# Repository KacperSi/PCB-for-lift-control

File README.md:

# PCB-for-lift-control
PCB design created in KiCad.

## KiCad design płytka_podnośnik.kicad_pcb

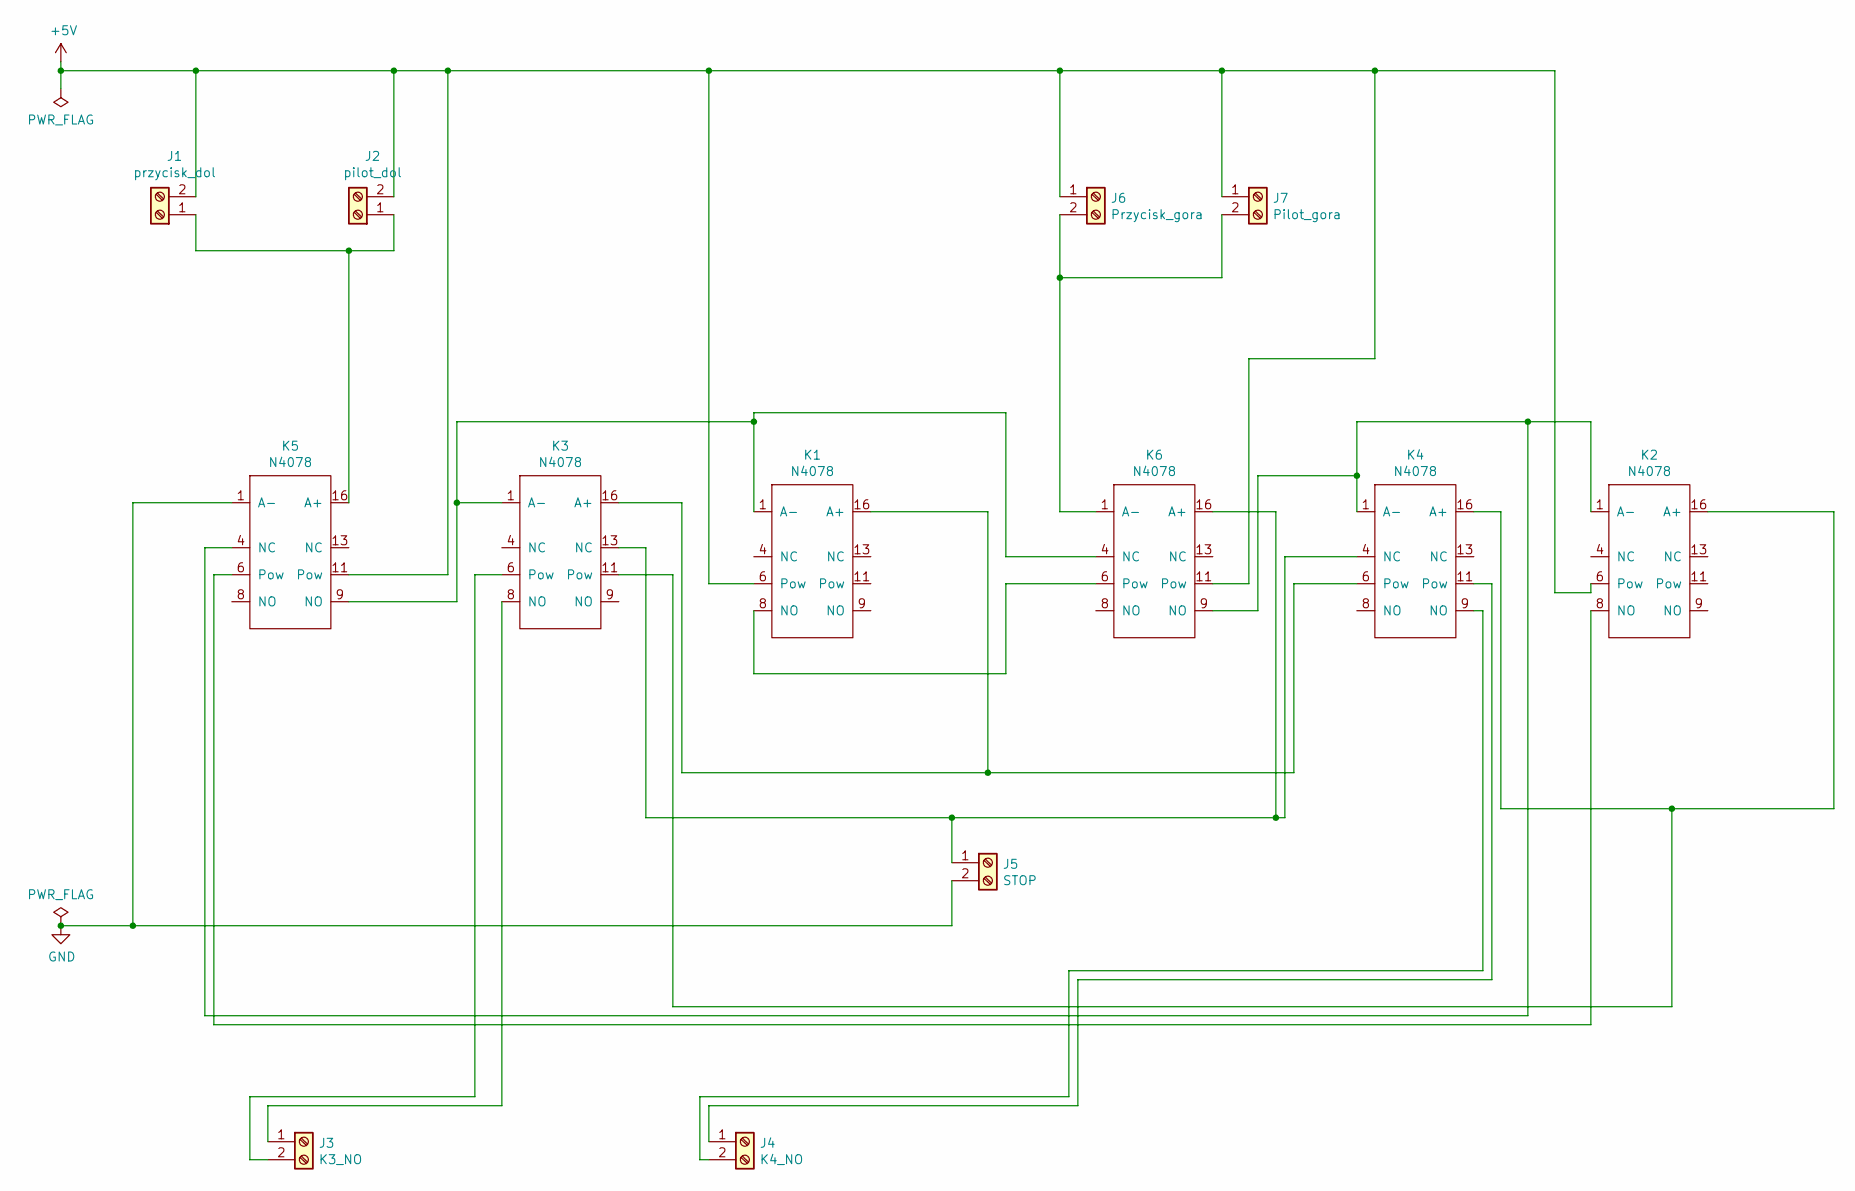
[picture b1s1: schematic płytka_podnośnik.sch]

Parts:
J1: przycisk_dol; TerminalBlock_Altech_AK300-2_P5.00mm
J2: pilot_dol; TerminalBlock_Altech_AK300-2_P5.00mm
J3: K3_NO; TerminalBlock_Altech_AK300-2_P5.00mm
J4: K4_NO; TerminalBlock_Altech_AK300-2_P5.00mm
J5: STOP; TerminalBlock_Altech_AK300-2_P5.00mm
J6: Przycisk_gora; TerminalBlock_Altech_AK300-2_P5.00mm
J7: Pilot_gora; TerminalBlock_Altech_AK300-2_P5.00mm
K1, K2, K3, K4, K5, K6: N4078; N4078-2C-5V-0.2W

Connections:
+5V: J1.2, J2.2, J6.1, J7.1, K1.6 (Pow), K2.6 (Pow), K5.11 (Pow), K6.11 (Pow)
GND: J5.2, K5.1 (A-)
unnamed: J1.1, J2.1, K5.16 (A+)
unnamed: J3.1, K3.8 (NO)
unnamed: J3.2, K3.6 (Pow)
unnamed: J4.1, K4.11 (Pow)
unnamed: J4.2, K4.9 (NO)
unnamed: J5.1, K3.13 (NC), K4.4 (NC), K6.16 (A+)
unnamed: J6.2, J7.2, K6.1 (A-)
unnamed: K1.1 (A-), K3.1 (A-), K5.9 (NO), K6.4 (NC)
unnamed: K1.8 (NO), K6.6 (Pow)
unnamed: K1.16 (A+), K3.16 (A+), K4.6 (Pow)
unnamed: K2.1 (A-), K4.1 (A-), K5.4 (NC), K6.9 (NO)
unnamed: K2.8 (NO), K5.6 (Pow)
unnamed: K2.16 (A+), K3.11 (Pow), K4.16 (A+)

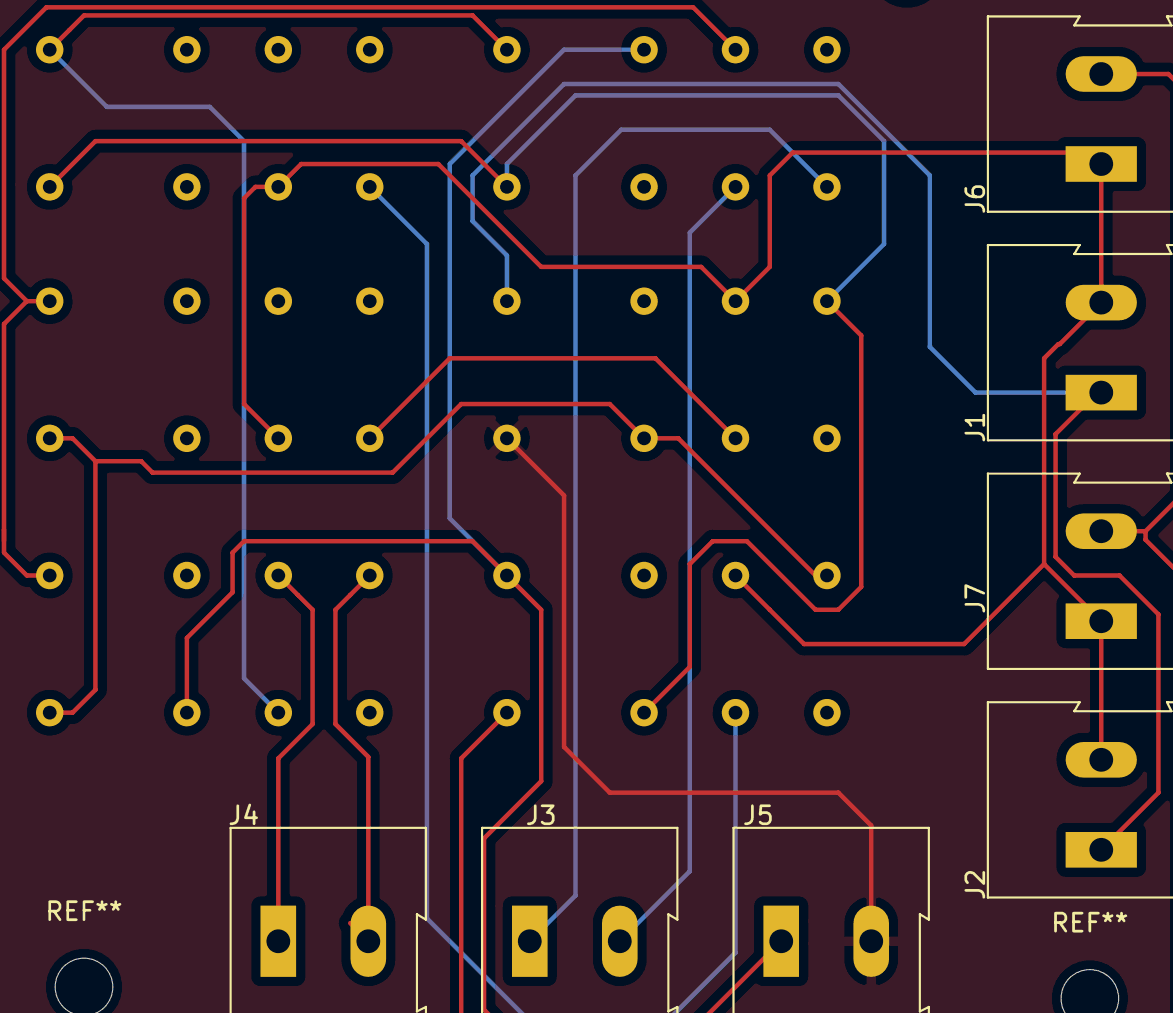
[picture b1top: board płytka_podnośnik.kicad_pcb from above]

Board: 2 copper layers, 13 parts (0 on the bottom side), 15 nets.

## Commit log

2021-09-21 final version
